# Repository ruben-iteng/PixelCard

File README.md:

<div align="center">

# PixelCard

<br/>

Business card generator with lots of blinky lights - PixelCard

</div>

## About
PixelCard is a business card generator with lots of blinky lights. It is a showcase for the versatility of faebryk, an open-source EDA (Electronic Design Automation) tool.
With PixelCard, you can create custom business cards that feature text filled with LEDs!
The project features:
- Auto-routing of the PCB
- Auto-placement of the components
- Design 100% defined in python
- Custom font support
- USB-C PD for power (5V)
- Over current protection
- ISO/IEC_7810 ID-1 credit card form factor

This project is build with the open-source EDA [faebryk](https://github.com/faebryk/faebryk).

## Working with the source files

See [here](https://hackaday.io/project/196784-pixelcard#menu-instructions) for the instructions on how to install and edit this project.

## Building

If you want to build the physical output of this project you can find the build instructions [here](./docs/build_instructions.md).

## Contributing

If you want to share your alterations, improvements, or add bugfixes to this project, please take a look at the [contributing guidelines](./docs/CONTRIBUTING.md).

## Community Support

Community support is provided via Discord; see the Resources below for details.

### Resources

- Hackaday.io: [Project Page](https://hackaday.io/project/196784-pixelcard)
- Source Code: [Github](https://github.com/ruben-iteng/pixelcard)
- Chat: Real-time chat happens in faebryk's Discord Server (chit-chat room for now). Use this Discord [Invite](https://discord.gg/95jYuPmnUW) to register
- Issues: [Issues](https://github.com/ruben-iteng/pixelcard/issues)

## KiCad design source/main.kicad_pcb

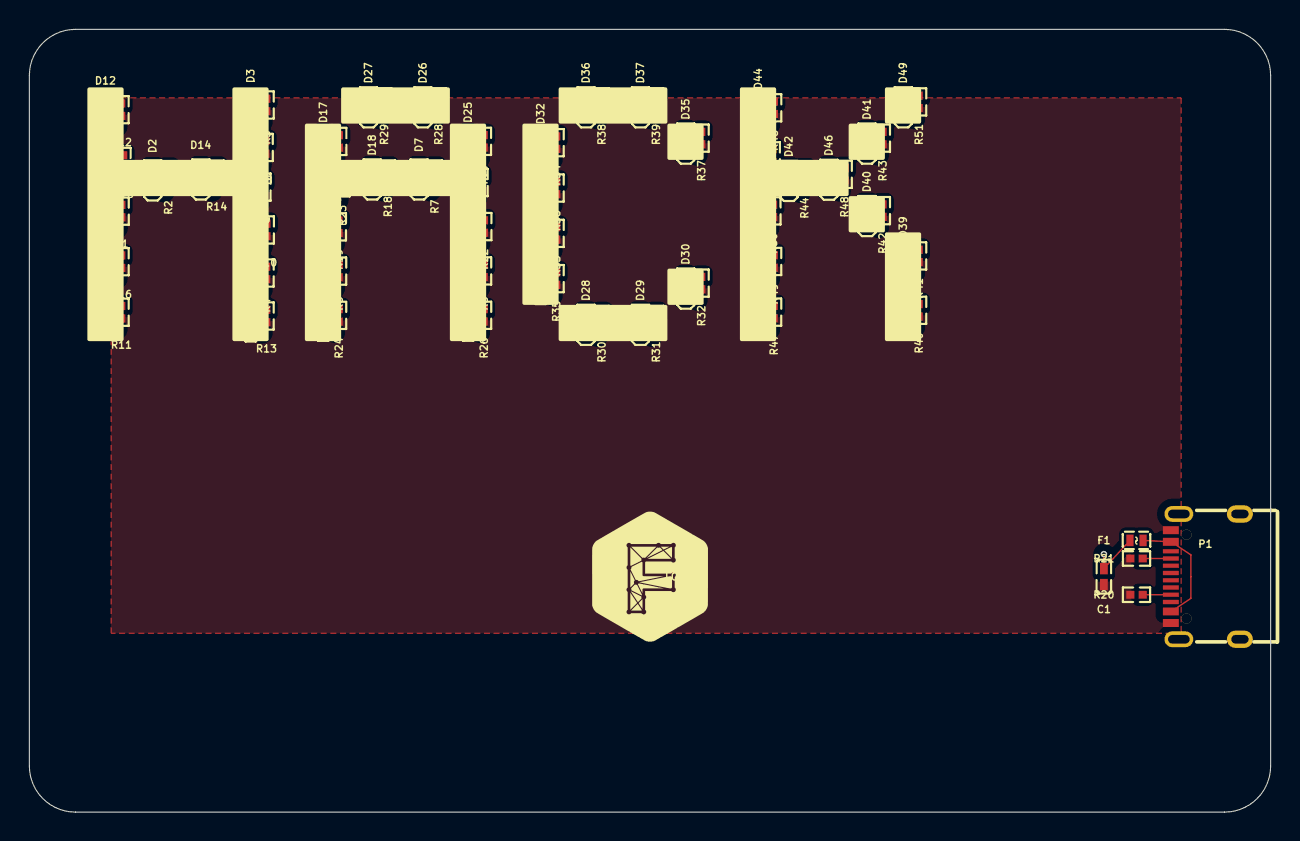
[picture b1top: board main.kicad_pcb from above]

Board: 2 copper layers, 85.6 x 54.0 mm, 104 parts (0 on the bottom side), 55 nets.

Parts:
C1: 100nF 16V X7R; C0402
D1, D2, D3, D4, D5, D6, D7, D8, D9, D10, D11, D12, D13, D14, D15, D16, D17, D18, D19, D20, D21, D22, D23, D24, D25, D26, D27, D28, D29, D30, D31, D32, D33, D34, D35, D36, D37, D38, D39, D40, D41, D42, D43, D44, D45, D46, D47, D48, D49: LED; LED0402-R-RD_RED
F1: Fuse; F0402
LOGO1: Faebryk_Logo; faebryk_logo
P1: USB_Type_C_Receptacle_16_pin; USB-C-SMD_TYPE-C-6PIN-2MD-073
R1, R2, R3, R4, R5, R6, R7, R8, R9, R10, R11, R12, R13, R14, R15, R16, R17, R18, R19, R22, R23, R24, R25, R26, R27, R28, R29, R30, R31, R32, R33, R34, R35, R36, R37, R38, R39, R40, R41, R42, R43, R44, R45, R46, R47, R48, R49, R50, R51: 100Ω; R0402
R20, R21: 5.1kΩ; R0402

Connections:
D1-1-R1-1: D1.1, R1.1
D2-1-R2-1: D2.1, R2.1
D3-1-R3-1: D3.1, R3.1
D4-1-R4-1: D4.1, R4.1
D5-1-R5-1: D5.1, R5.1
D6-1-R6-1: D6.1, R6.1
D7-1-R7-1: D7.1, R7.1
D8-1-R8-1: D8.1, R8.1
D9-1-R9-1: D9.1, R9.1
D10-1-R10-1: D10.1, R10.1
D11-1-R11-1: D11.1, R11.1
D12-1-R12-1: D12.1, R12.1
D13-1-R13-1: D13.1, R13.1
D14-1-R14-1: D14.1, R14.1
D15-1-R15-1: D15.1, R15.1
D16-1-R16-1: D16.1, R16.1
D17-1-R17-1: D17.1, R17.1
D18-1-R18-1: D18.1, R18.1
D19-1-R19-1: D19.1, R19.1
D20-1-R22-1: D20.1, R22.1
D21-1-R23-1: D21.1, R23.1
D22-1-R24-1: D22.1, R24.1
D23-1-R25-1: D23.1, R25.1
D24-1-R26-1: D24.1, R26.1
D25-1-R27-1: D25.1, R27.1
D26-1-R28-1: D26.1, R28.1
D27-1-R29-1: D27.1, R29.1
D28-1-R30-1: D28.1, R30.1
D29-1-R31-1: D29.1, R31.1
D30-1-R32-1: D30.1, R32.1
D31-1-R33-1: D31.1, R33.1
D32-1-R34-1: D32.1, R34.1
D33-1-R35-1: D33.1, R35.1
D34-1-R36-1: D34.1, R36.1
D35-1-R37-1: D35.1, R37.1
D36-1-R38-1: D36.1, R38.1
D37-1-R39-1: D37.1, R39.1
D38-1-R40-1: D38.1, R40.1
D39-1-R41-1: D39.1, R41.1
D40-1-R42-1: D40.1, R42.1
D41-1-R43-1: D41.1, R43.1
D42-1-R44-1: D42.1, R44.1
D43-1-R45-1: D43.1, R45.1
D44-1-R46-1: D44.1, R46.1
D45-1-R47-1: D45.1, R47.1
D46-1-R48-1: D46.1, R48.1
D47-1-R49-1: D47.1, R49.1
D48-1-R50-1: D48.1, R50.1
D49-1-R51-1: D49.1, R51.1
F1-1-P1-11-P1-2: F1.1, P1.2, P1.11
P1-4-R20-1: P1.4, R20.1
P1-9-R21-1: P1.9, R21.1
P1-13-P1-14: P1.13, P1.14
gnd: C1.2, P1.1, P1.12, R1.2, R2.2, R3.2, R4.2, R5.2, R6.2, R7.2, R8.2, R9.2, R10.2, R11.2, R12.2, R13.2, R14.2, R15.2, R16.2, R17.2, R18.2, R19.2, R20.2, R21.2, R22.2, R23.2, R24.2, R25.2, R26.2, R27.2, R28.2, R29.2, R30.2, R31.2, R32.2, R33.2, R34.2, R35.2, R36.2, R37.2, R38.2, R39.2, R40.2, R41.2, R42.2, R43.2, R44.2, R45.2, R46.2, R47.2, R48.2, R49.2, R50.2, R51.2
vbus: C1.1, D1.2, D2.2, D3.2, D4.2, D5.2, D6.2, D7.2, D8.2, D9.2, D10.2, D11.2, D12.2, D13.2, D14.2, D15.2, D16.2, D17.2, D18.2, D19.2, D20.2, D21.2, D22.2, D23.2, D24.2, D25.2, D26.2, D27.2, D28.2, D29.2, D30.2, D31.2, D32.2, D33.2, D34.2, D35.2, D36.2, D37.2, D38.2, D39.2, D40.2, D41.2, D42.2, D43.2, D44.2, D45.2, D46.2, D47.2, D48.2, D49.2, F1.2

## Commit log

2024-06-28 init repository
2024-06-28 Add basics
2024-06-30 Add WIP layout
2024-06-30 Better hierarchy layout; Fix pcb transform on no netlist change
2024-06-30 Fix layout
2024-06-30 Use new hierarchical layout
2024-06-30 wip:
    - add outline with rounded corners
    - add logo
    - add more layout
    - insert vias for vbus anode led
    - move designators
2024-07-01 Rename edgecut function; Set correct creditcard corner radius
2024-07-01 Add routing & Changed some layout things
2024-07-02 Rerun, only F, no connect
2024-07-02 Fix GR_Text
2024-07-02 Run pre-commit
2024-07-02 Update component placement
2024-07-02 Basic vias
2024-07-02 Add gnd zone on top layer (disabled)
2024-07-02 Improved reso & moved net routing
2024-07-02 Enhance cli help; Add text input cli argument
2024-07-02 Contact info & Some params
2024-07-02 Text anchor; Font downloader
2024-07-02 Rerender
2024-07-02 Update back layout and put rpi pinout cheatsheet
2024-07-02 Set correct faebryk branch
2024-07-02 Revision 1.0.0 (#1)
    ---------
2024-07-04 Improve routing
2024-07-05 Layout: improve font rendering
    Use updated FontLayout
    Group font settings in app.py
    Render silk zones for text polygons
2024-07-05 Enable artifacts
2024-07-05 Remove actual artifacts
2024-07-06 Use newest app lib in faebryk
2024-07-06 Adjust font parameters
2024-07-06 Improve routing & Enable artifacts & Improve font (#2)
    * Improve routing
    * Layout: improve font rendering
    Use updated FontLayout
    Group font settings in app.py
    Render silk zones for text polygons
    * Enable artifacts

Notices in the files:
README.md:
License: MIT
